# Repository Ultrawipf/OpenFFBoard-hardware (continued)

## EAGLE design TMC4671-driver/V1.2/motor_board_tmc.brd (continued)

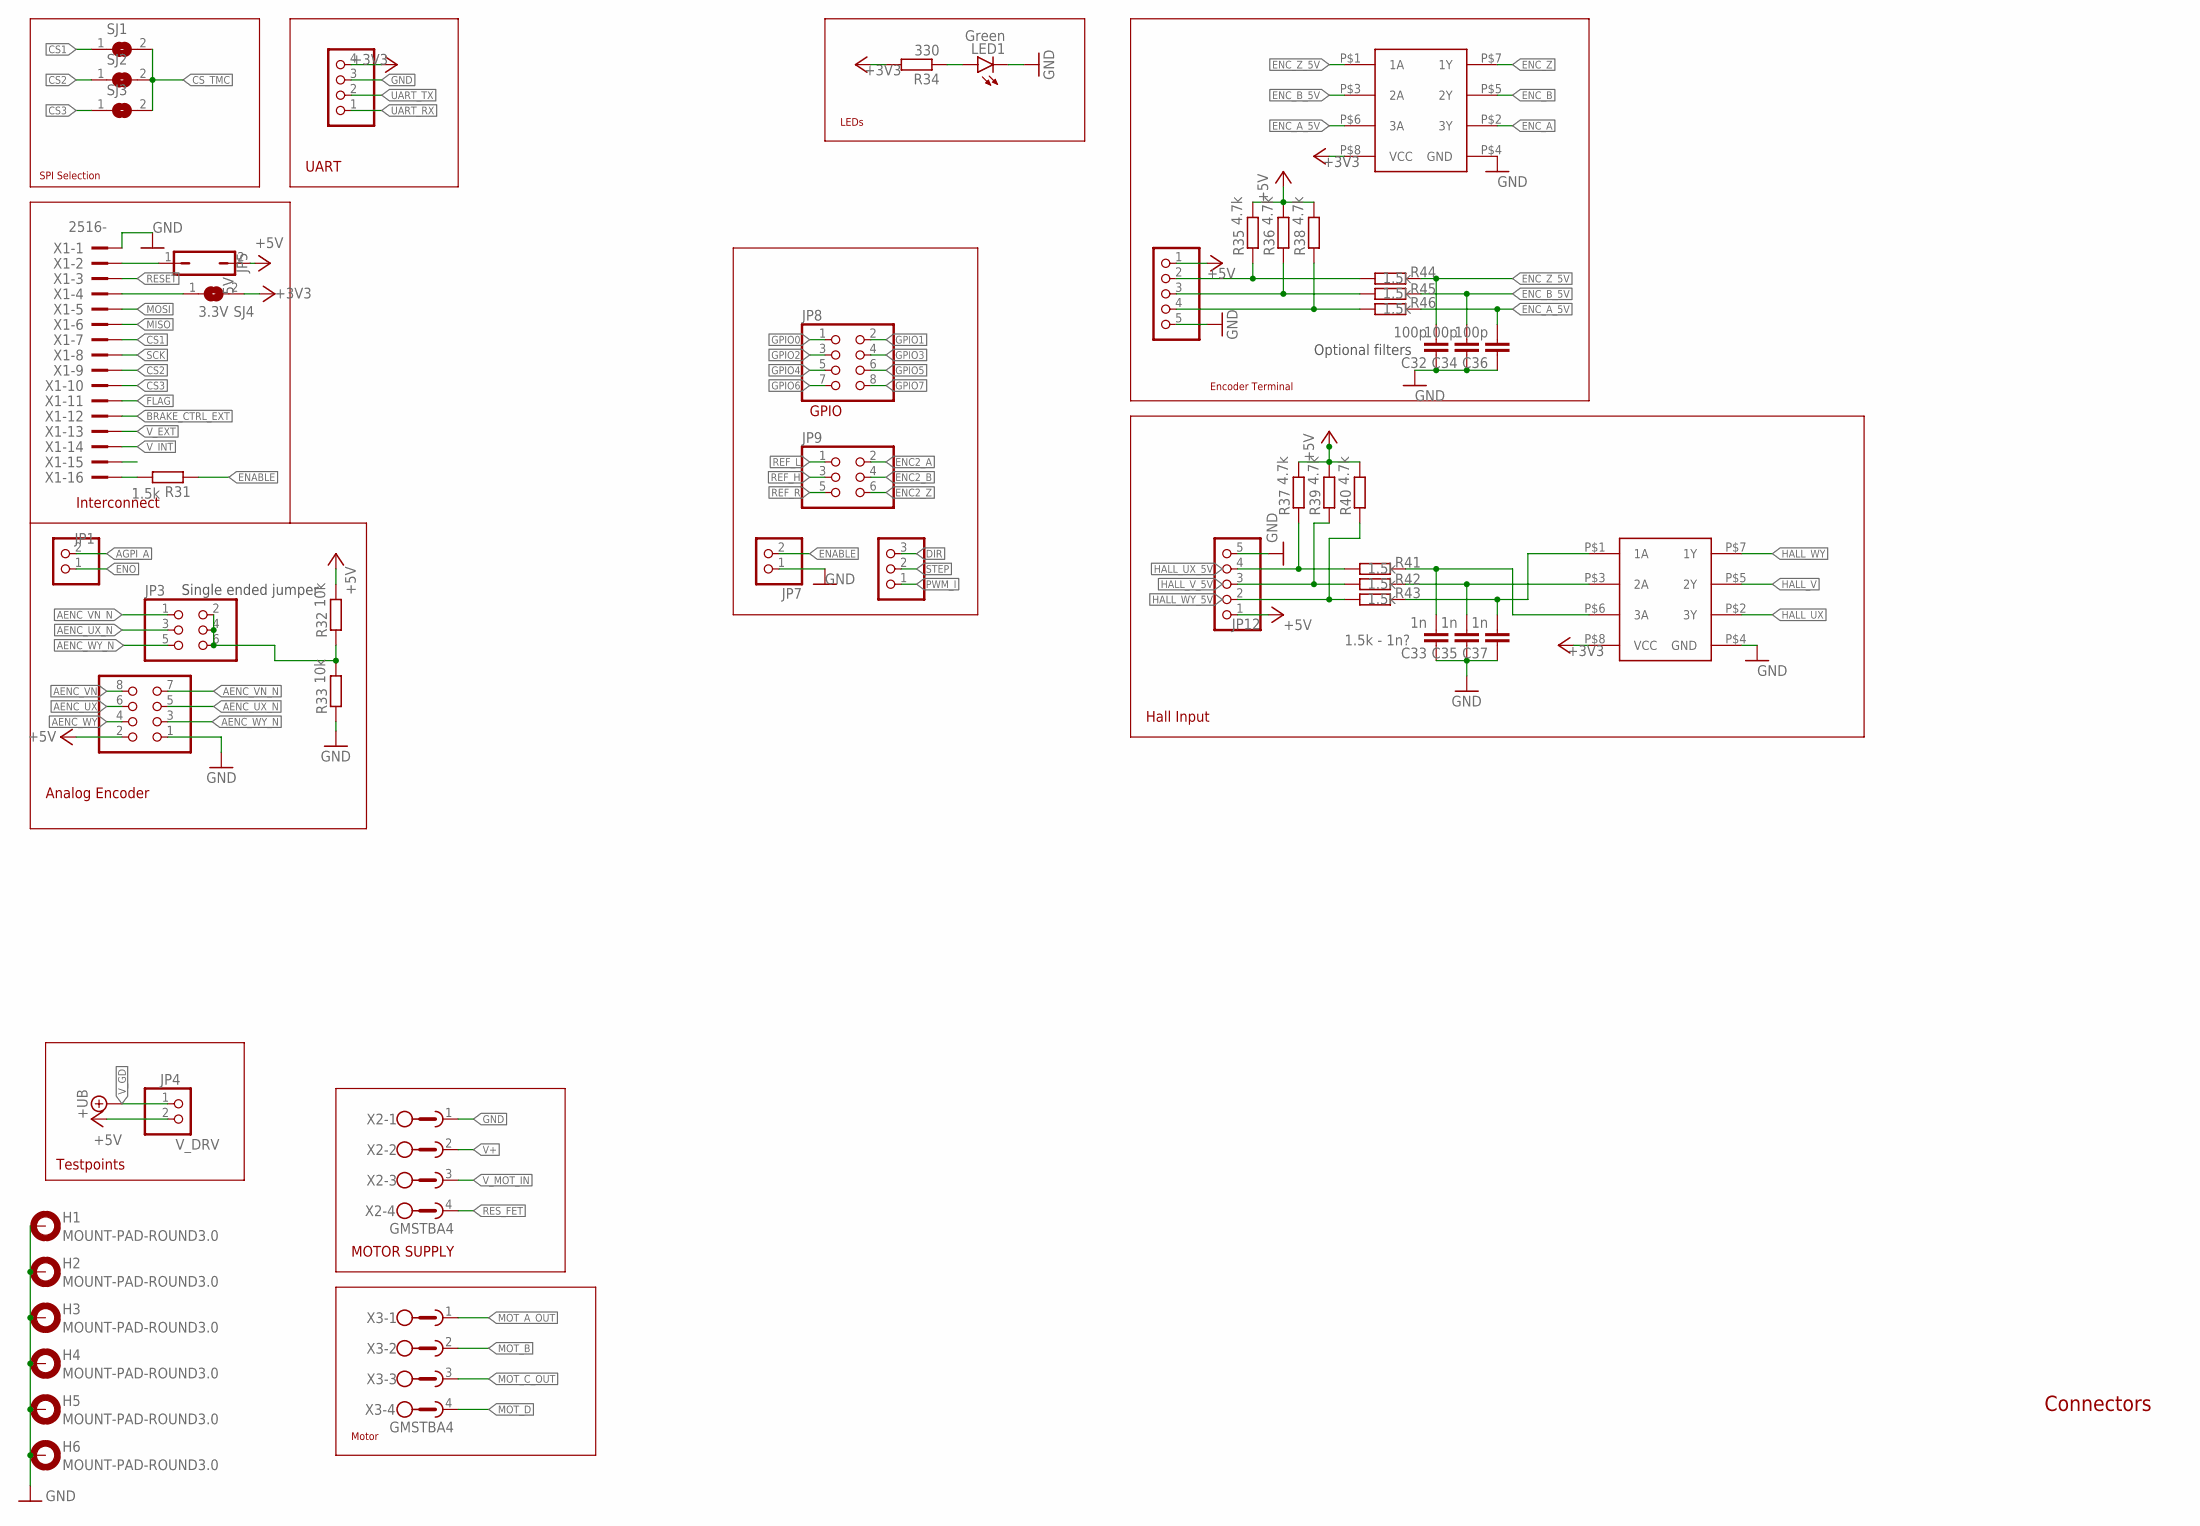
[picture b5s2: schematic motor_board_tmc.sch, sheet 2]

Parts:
C32, C34, C36: 100p; C0603
C33, C35, C37: 1n; C0603
H1, H2, H3, H4, H5, H6: MOUNT-PAD-ROUND3.0; 3,0-PAD
JP1, JP7: PINHD-1X2; 1X02
JP2, JP8: PINHD-2X4; 2X04
JP3, JP9: PINHD-2X3; 2X03
JP4: V_DRV; 1X02
JP5: 5V; JP1
JP6: PINHD-1X4; 1X04
JP10: PINHD-1X3; 1X03
JP11, JP12: PINHD-1X5; 1X05
LED1: Green; SML0805
R31, R41, R42, R43, R44, R45, R46: 1.5k; R0603
R32, R33: 10k; R0603
R34: 330; R0603
R35, R36, R37, R38, R39, R40: 4.7k; R0603
SJ1, SJ2, SJ3: SJ
SJ4: 3.3V; SJ
U18, U19: NC7NZ17K8X-3-BUFFER; VFSOP-8
X1: 2516-; PAK100/2500-16
X2, X3: GMSTBA4

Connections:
+3V3: JP6.4, R34.2, SJ4.2, U18.P$8 (VCC), U19.P$8 (VCC); also elsewhere on the board
+5V: JP2.2, JP4.2, JP5.2, JP11.1, JP12.1, R32.2, R35.2, R36.2, R37.2, R38.2, R39.2, R40.2; also elsewhere on the board
AENC_UX: JP2.6; also elsewhere on the board
AENC_UX_N: JP2.5, JP3.3; also elsewhere on the board
AENC_VN: JP2.8; also elsewhere on the board
AENC_VN_N: JP2.7, JP3.1; also elsewhere on the board
AENC_WY: JP2.4; also elsewhere on the board
AENC_WY_N: JP2.3, JP3.5; also elsewhere on the board
AGPI_A: JP1.2; also elsewhere on the board
BRAKE_CTRL_EXT: X1.12; also elsewhere on the board
CS1: SJ1.1, X1.7
CS2: SJ2.1, X1.9
CS3: SJ3.1, X1.10
CS_TMC: SJ1.2, SJ2.2, SJ3.2; also elsewhere on the board
DIR: JP10.3; also elsewhere on the board
ENABLE: JP7.2, R31.1; also elsewhere on the board
ENC2_A: JP9.2; also elsewhere on the board
ENC2_B: JP9.4; also elsewhere on the board
ENC2_Z: JP9.6; also elsewhere on the board
ENC_A: U18.P$2 (3Y); also elsewhere on the board
ENC_A_5V: C36.2, R46.1, U18.P$6 (3A)
ENC_B: U18.P$5 (2Y); also elsewhere on the board
ENC_B_5V: C34.2, R45.1, U18.P$3 (2A)
ENC_Z: U18.P$7 (1Y); also elsewhere on the board
ENC_Z_5V: C32.2, R44.1, U18.P$1 (1A)
ENO: JP1.1; also elsewhere on the board
FLAG: X1.11; also elsewhere on the board
GND: C32.1, C33.1, C34.1, C35.1, C36.1, C37.1, H1.B3,0, H2.B3,0, H3.B3,0, H4.B3,0, H5.B3,0, H6.B3,0, JP2.1, JP6.3, JP7.1, JP11.5, JP12.5, LED1.C, R33.1, U18.P$4 (GND), U19.P$4 (GND), X1.1, X2.1; also elsewhere on the board
GPIO0: JP8.1; also elsewhere on the board
GPIO1: JP8.2; also elsewhere on the board
GPIO2: JP8.3; also elsewhere on the board
GPIO3: JP8.4; also elsewhere on the board
GPIO4: JP8.5; also elsewhere on the board
GPIO5: JP8.6; also elsewhere on the board
GPIO6: JP8.7; also elsewhere on the board
GPIO7: JP8.8; also elsewhere on the board
HALL_UX: U19.P$2 (3Y); also elsewhere on the board
HALL_UX_5V: C33.2, R41.1, U19.P$6 (3A)
HALL_V: U19.P$5 (2Y); also elsewhere on the board
HALL_V_5V: C35.2, R42.1, U19.P$3 (2A)
HALL_WY: U19.P$7 (1Y); also elsewhere on the board
HALL_WY_5V: C37.2, R43.1, U19.P$1 (1A)
MISO: X1.6; also elsewhere on the board
MOSI: X1.5; also elsewhere on the board
MOT_A_OUT: X3.1; also elsewhere on the board
MOT_B: X3.2; also elsewhere on the board
MOT_C_OUT: X3.3; also elsewhere on the board
MOT_D: X3.4; also elsewhere on the board
unnamed: JP12.4, R37.1, R41.2
unnamed: JP12.3, R39.1, R42.2
unnamed: JP11.4, R38.1, R46.2
unnamed: LED1.A, R34.1
unnamed: JP11.3, R36.1, R45.2
unnamed: JP11.2, R35.1, R44.2
unnamed: JP12.2, R40.1, R43.2
unnamed: R31.2, X1.16
unnamed: SJ4.1, X1.4
unnamed: JP3.2, JP3.4, JP3.6, R32.1, R33.2
unnamed: JP5.1, X1.2
PWM_I: JP10.1; also elsewhere on the board
REF_H: JP9.3; also elsewhere on the board
REF_L: JP9.1; also elsewhere on the board
REF_R: JP9.5; also elsewhere on the board
RESET: X1.3; also elsewhere on the board
RES_FET: X2.4; also elsewhere on the board
SCK: X1.8; also elsewhere on the board
STEP: JP10.2; also elsewhere on the board
UART_RX: JP6.1; also elsewhere on the board
UART_TX: JP6.2; also elsewhere on the board
V+: X2.2; also elsewhere on the board
V_EXT: X1.13; also elsewhere on the board
V_GD: JP4.1; also elsewhere on the board
V_INT: X1.14; also elsewhere on the board
V_MOT_IN: X2.3; also elsewhere on the board

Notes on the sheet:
Motor
Encoder Terminal
Hall Input
GPIO
MOTOR SUPPLY
Interconnect
UART
SPI Selection
LEDs
Connectors
Testpoints
Analog Encoder
Single ended jumper
1.5k - 1n?
Optional filters

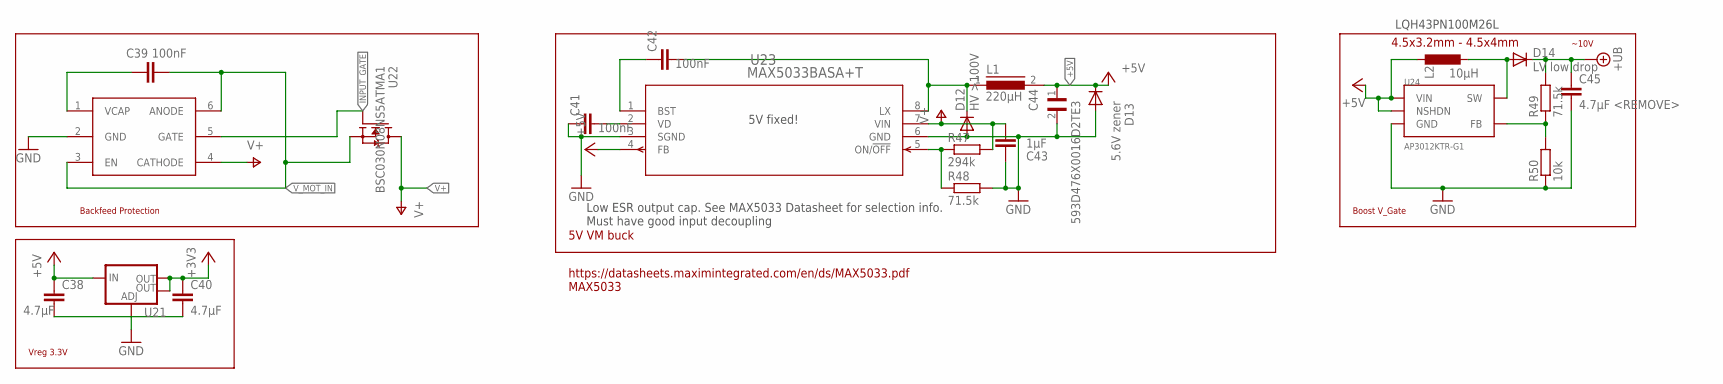
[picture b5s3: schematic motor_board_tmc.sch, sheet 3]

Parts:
C38, C40: 4.7µF; C0805
C39: 100nF; C0805
C41, C42: 100nF; C0603
C43: 1µF; C1206
C44: 593D476X0016D2TE3; CAPPM7343X310N
C45: 4.7µF <REMOVE>; C0805
D12: HV >100V; SOD-123FL
D13: 5.6V zener; SOD-123FL
D14: LV low drop; SOD-123FL
L1: 220µH; 8MMINDUCTOR
L2: 10µH; L4532P
R47: 294k; R0805
R48, R49: 71.5k; R0805
R50: 10k; R0603
U20: LM74700-Q1; SOT23-6
U21: V_REG_LM1117SOT223; SOT223
U22: BSC030N08NS5ATMA1; MOSFET_BSC093N04LSGATMA1
U23: MAX5033BASA+T; 21-0041B_8_MXM
U24: AP3012KTR-G1; SOT23-5L

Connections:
+3V3: C40.1, U21.2 (OUT), U21.4 (OUT); also elsewhere on the board
+5V: C38.1, C44.1, D13.C, L1.2, L2.1, U21.3 (IN), U23.4 (FB), U24.4 (NSHDN), U24.5 (VIN); also elsewhere on the board
GND: C38.2, C40.2, C41.1, C43.1, C44.2, C45.2, D12.A, D13.A, R48.2, R50.1, U20.2 (GND), U21.1 (ADJ), U23.3 (SGND), U23.6 (GND), U24.2 (GND); also elsewhere on the board
INPUT_GATE: U20.5 (GATE), U22.4 (G)
unnamed: R49.1, R50.2, U24.3 (FB)
unnamed: D14.A, L2.2, U24.1 (SW)
unnamed: C42.2, D12.C, L1.1, U23.8 (LX)
unnamed: C42.1, U23.1 (BST)
unnamed: R47.1, R48.1, U23.5 (ON/!OFF)
unnamed: C39.1, U20.1 (VCAP)
unnamed: C41.2, U23.2 (VD)
V+: C43.2, R47.2, U20.4 (CATHODE), U22.5 (D), U23.7 (VIN); also elsewhere on the board
V_GD: C45.1, D14.C, R49.2; also elsewhere on the board
V_MOT_IN: C39.2, U20.3 (EN), U20.6 (ANODE), U22.1 (S), U22.2 (S), U22.3 (S); also elsewhere on the board

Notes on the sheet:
Vreg 3.3V
Backfeed Protection
Boost V_Gate
~10V
4.5x3.2mm - 4.5x4mm
5V VM buck
https://datasheets.maximintegrated.com/en/ds/MAX5033.pdf MAX5033
5V fixed!
LQH43PN100M26L
Low ESR output cap. See MAX5033 Datasheet for selection info. Must have good input decoupling

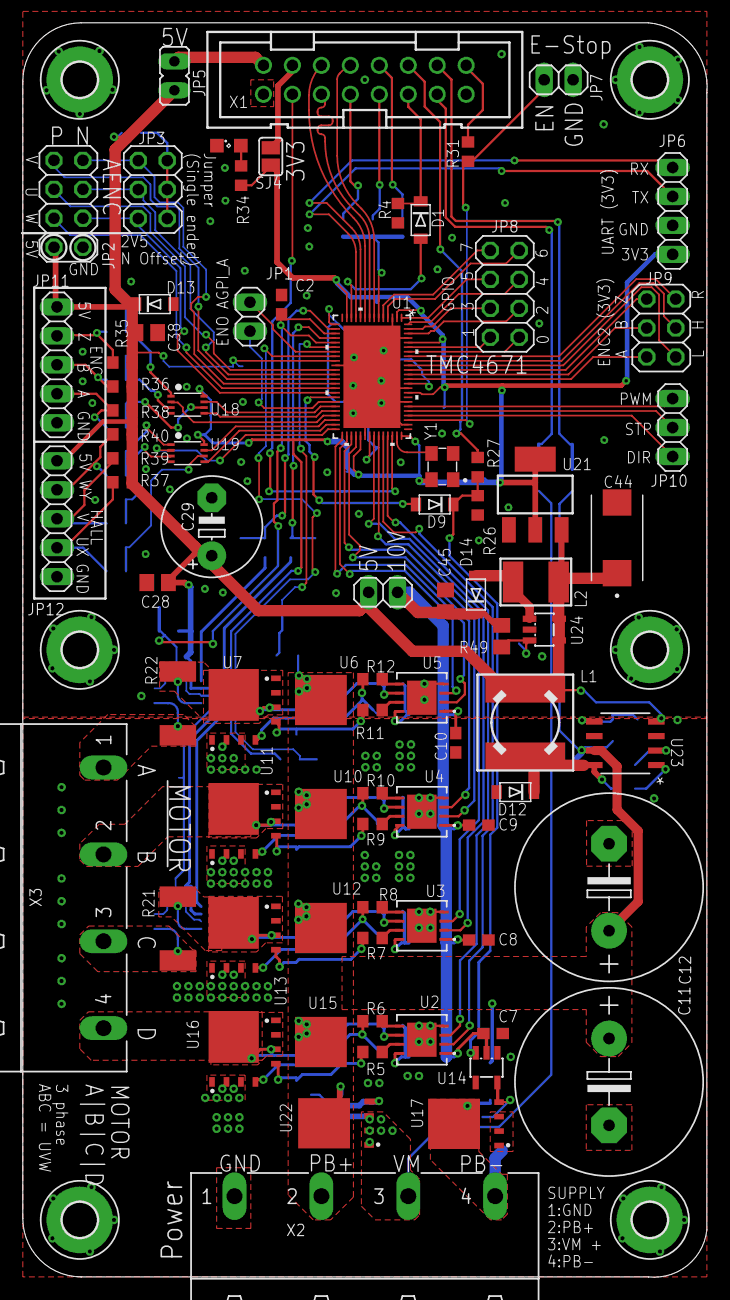
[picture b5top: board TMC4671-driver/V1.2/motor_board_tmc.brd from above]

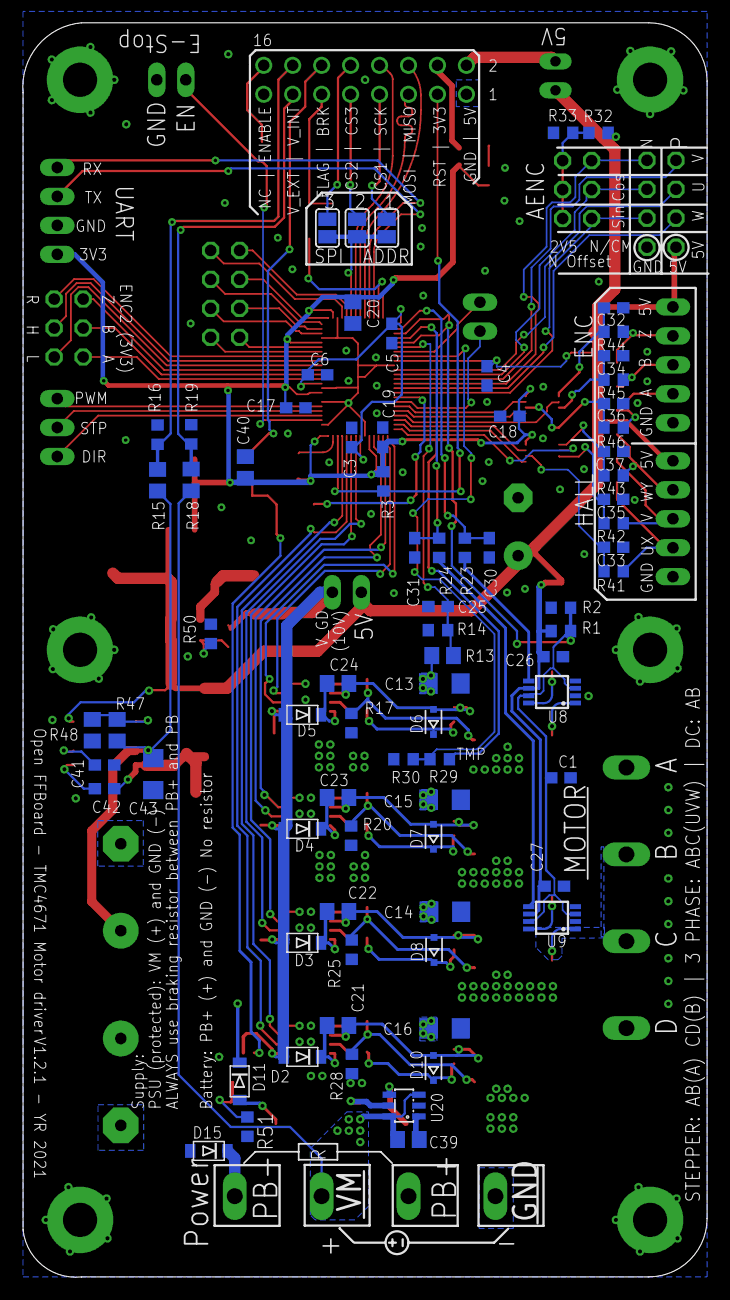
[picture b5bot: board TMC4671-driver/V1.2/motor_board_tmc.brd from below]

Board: 2 copper layers, 60.0 x 110.0 mm, 164 parts (78 on the bottom side), 125 nets.

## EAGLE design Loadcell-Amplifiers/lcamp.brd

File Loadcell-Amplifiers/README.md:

## INA333 3-wire Loadcell amplifier

Connections:
###
- Vin   :   3.3V/5V supply and load cell positive
- GND   :   GND and load cell negative
- IN    :   Load cell center/signal
- OUT   :   Amplified signal. Connect to ADC input

Gain setting: 10-1000, Clockwise rotation to increase
Offset: Clockwise to move the output up, ccw to move the output down to GND

Retune the offset when changing the gain and carefully check the output voltage to get the offset perfect.

The CPL and BOM files contain LCSC part numbers and be used on [JLCPCB](jlcpcb.com/).

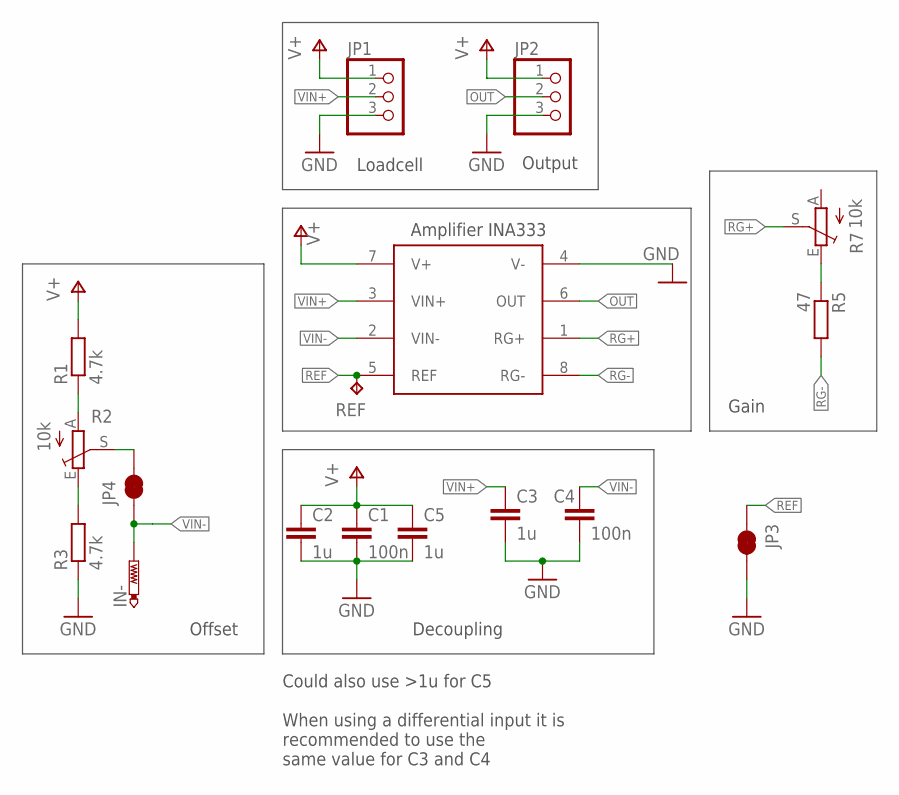
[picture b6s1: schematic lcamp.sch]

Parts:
C1, C4: 100n; C0603
C2, C3, C5: 1u; C0603
IN-: PTR1PAD1-13; P1-13
JP1, JP2: PINHD-1X3; 1X03
JP3, JP4: JUMPER-SMT_2_NC_TRACE_SILK; SMT-JUMPER_2_NC_TRACE_SILK
R1, R3: 4.7k; R0603
R2, R7: 10k; RJ9W
R5: 47; R0603
REF: TPB1,27; B1,27
U1: INA333MSOP8; MSOP8

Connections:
GND: C1.2, C2.2, C3.2, C4.2, C5.2, JP1.3, JP2.3, JP3.2, R3.1, U1.4 (V-)
unnamed: R5.1, R7.E
unnamed: R1.1, R2.A
unnamed: R2.E, R3.2
unnamed: JP4.2, R2.S
OUT: JP2.2, U1.6 (OUT)
REF: JP3.1, REF.TP, U1.5 (REF)
RG+: R7.S, U1.1 (RG+)
RG-: R5.2, U1.8 (RG-)
V+: C1.1, C2.1, C5.1, JP1.1, JP2.1, R1.2, U1.7 (V+)
VIN+: C3.1, JP1.2, U1.3 (VIN+)
VIN-: C4.1, IN-.TP, JP4.1, U1.2 (VIN-)

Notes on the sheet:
Offset
Gain
Loadcell
Output
Amplifier INA333
Decoupling
Could also use >1u for C5 When using a differential input it is recommended to use the same value for C3 and C4

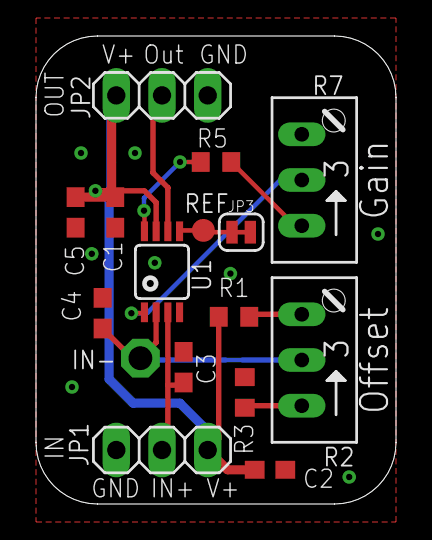
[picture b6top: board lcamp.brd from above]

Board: 2 copper layers, 20.0 x 26.0 mm, 17 parts (1 on the bottom side), 12 nets.

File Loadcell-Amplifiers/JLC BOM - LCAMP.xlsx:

Comment | Designator | Footprint | LCSC Part #
INA333 | U1 | MSOP-8 | C19450
10k pot | R2,R7 | THT | C118954
1µ Capacitor | C2,C3,C5 | C0603 | C15849
4.7k Resistor | R1, R3 | R0603 | C23162
47 Ohm Resistor | R5 | R0603 | C23182
100n Capacitor | C4, C1 | C0603 | C14663

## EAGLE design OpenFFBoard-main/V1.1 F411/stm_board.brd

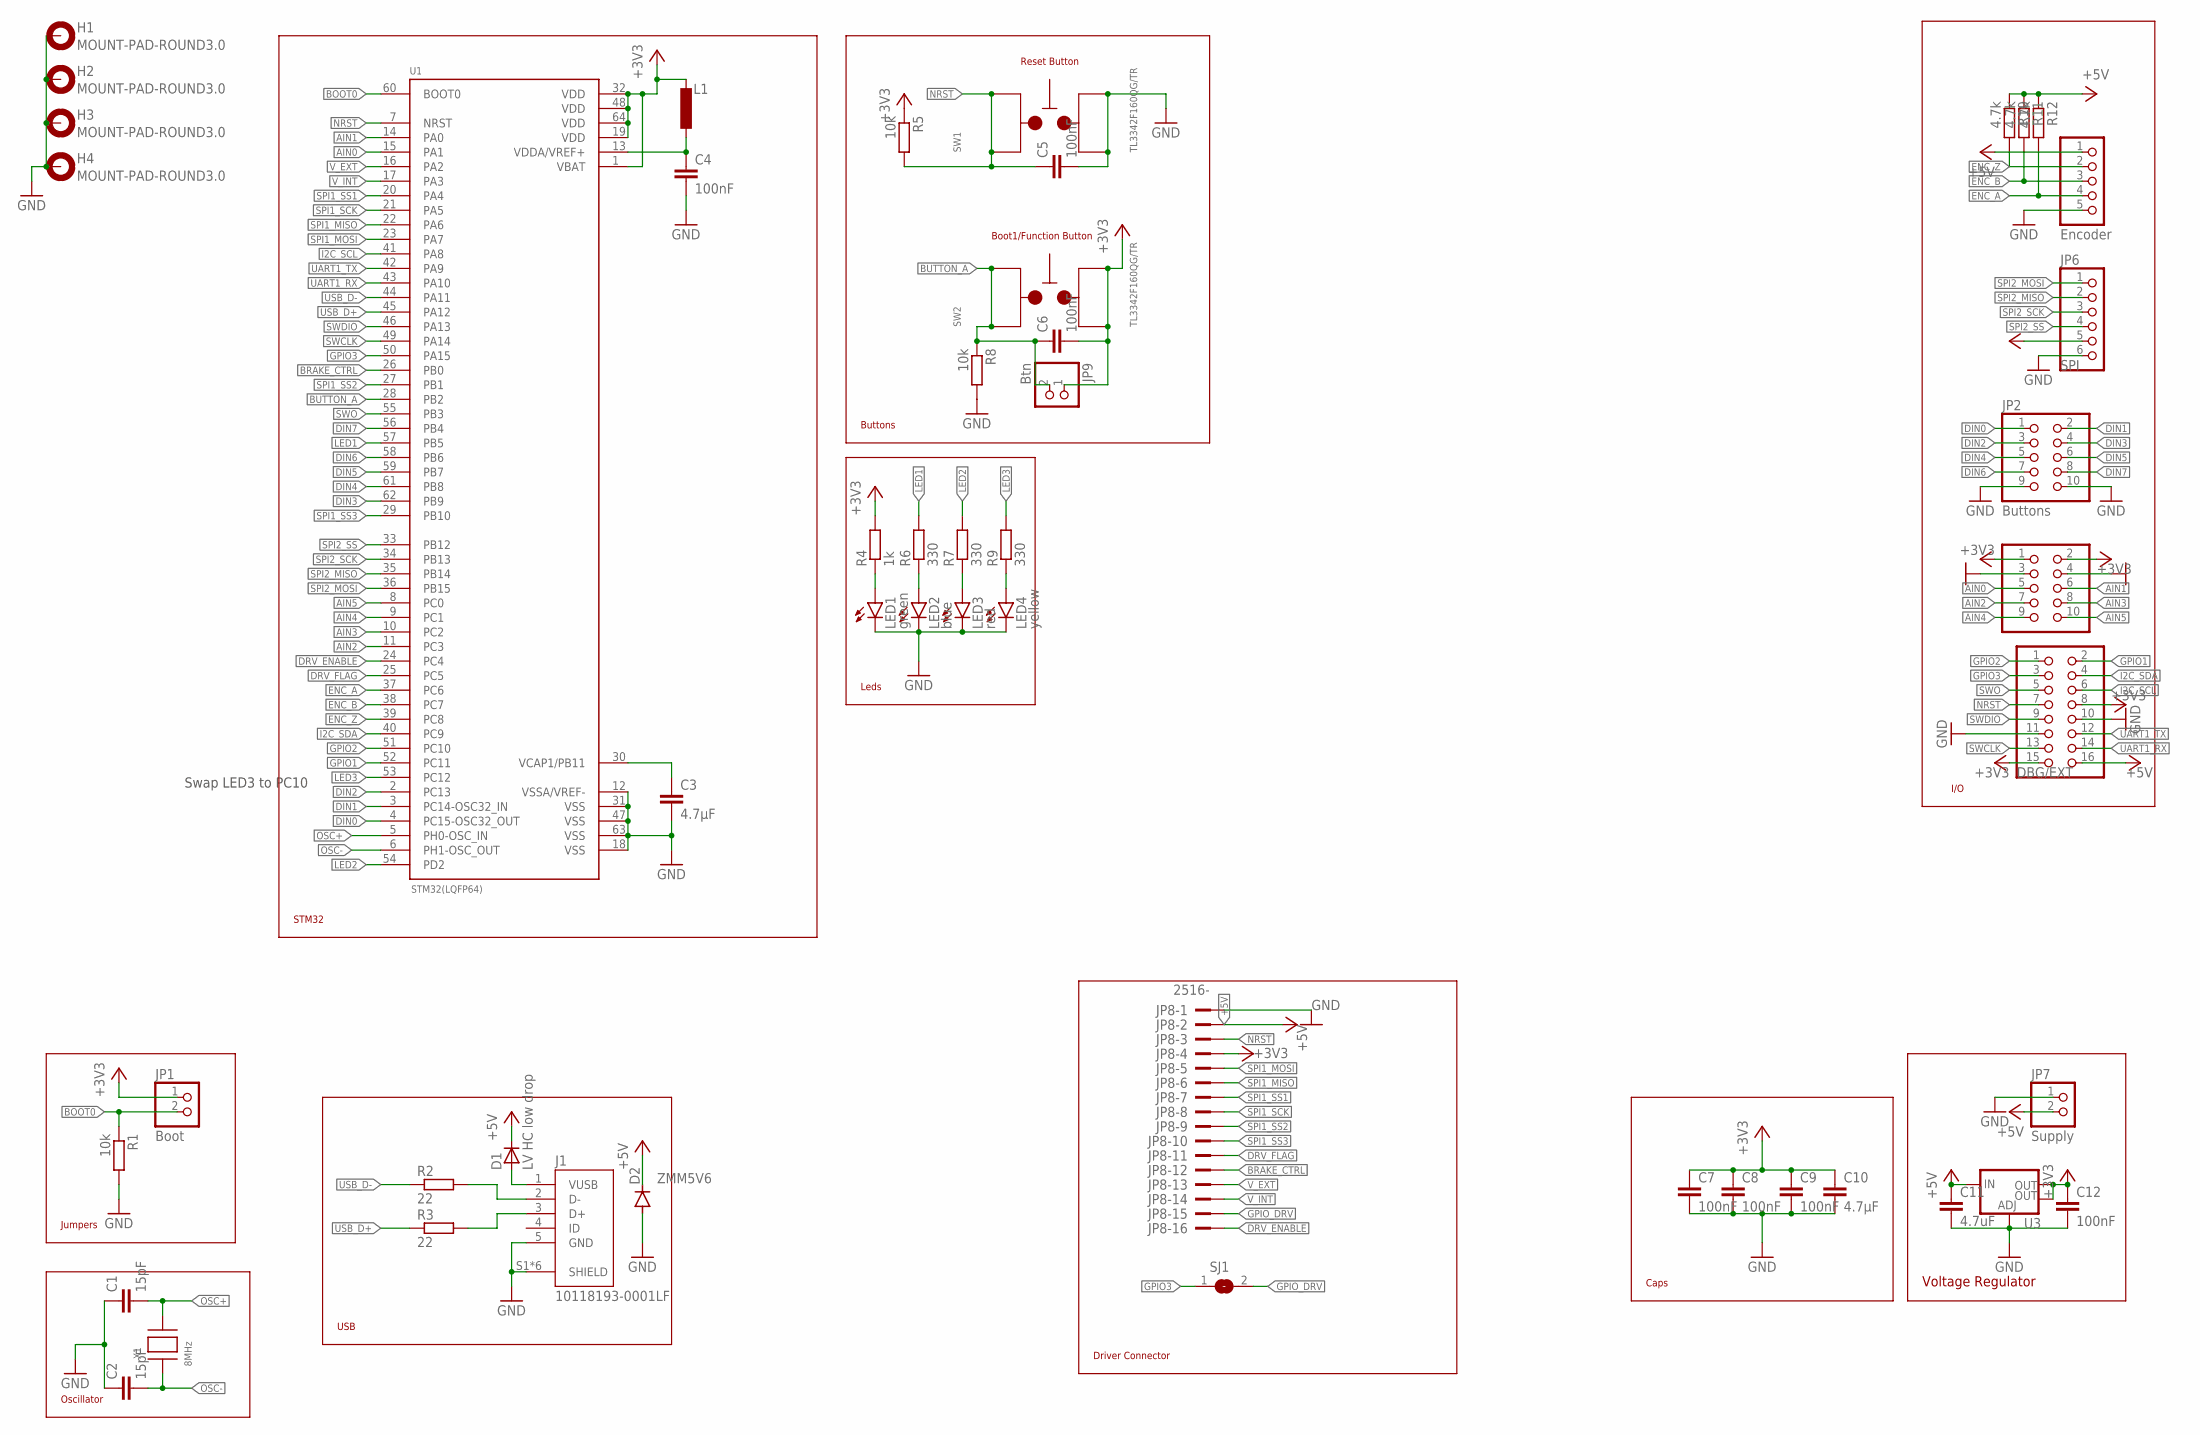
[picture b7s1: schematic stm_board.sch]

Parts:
C1, C2: 15pF; C0603
C3, C10: 4.7µF; C0805
C4, C5, C6, C7, C8, C9, C12: 100nF; C0603
C11: 4.7uF; C0805
D1: LV HC low drop; SMADIODE
D2: ZMM5V6; MINIMELF
H1, H2, H3, H4: MOUNT-PAD-ROUND3.0; 3,0-PAD
J1: 10118193-0001LF; FCI_10118193-0001LF
JP1: Boot; 1X02
JP2: Buttons; 2X05
JP3: Analog; 2X05
JP4: DBG/EXT; 2X08
JP5: Encoder; 1X05
JP6: SPI; 1X06
JP7: Supply; 1X02
JP8: 2516-; PAK100/2500-16
JP9: Btn; 1X02
L1: 2.2µH; L2012C
LED1: green; CHIPLED_0805
LED2: blue; CHIPLED_0805
LED3: red; CHIPLED_0805
LED4: yellow; CHIPLED_0805
R1, R5, R8: 10k; R0603
R2, R3: 22; R0603
R4: 1k; R0603
R6, R7, R9: 330; R0603
R10, R11, R12: 4.7k; R0603
SJ1: SJ
SW1, SW2: TL3342F160QG/TR
U1: STM32(LQFP64); QFP50P1200X1200X160-64N
U3: V_REG_LM1117SOT223; SOT223
X1: 8MHz; NX5032

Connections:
+3V3: C6.2, C7.1, C8.1, C9.1, C10.1, C12.1, JP1.1, JP3.1, JP3.2, JP4.8, JP4.15, JP6.5, JP8.4, JP9.1, L1.1, R4.2, R5.1, SW2.1, SW2.2, U1.1 (VBAT), U1.19 (VDD), U1.32 (VDD), U1.48 (VDD), U1.64 (VDD), U3.2 (OUT), U3.4 (OUT)
+5V: C11.1, D1.C, D2.C, JP4.16, JP5.1, JP7.2, JP8.2, R10.1, R11.1, R12.1, U3.3 (IN)
AIN0: JP3.5, U1.15 (PA1)
AIN1: JP3.6, U1.14 (PA0)
AIN2: JP3.7, U1.11 (PC3)
AIN3: JP3.8, U1.10 (PC2)
AIN4: JP3.9, U1.9 (PC1)
AIN5: JP3.10, U1.8 (PC0)
BOOT0: JP1.2, R1.1, U1.60 (BOOT0)
BRAKE_CTRL: JP8.12, U1.26 (PB0)
BUTTON_A: C6.1, JP9.2, R8.1, SW2.3, SW2.4, U1.28 (PB2)
DIN0: JP2.1, U1.4 (PC15-OSC32_OUT)
DIN1: JP2.2, U1.3 (PC14-OSC32_IN)
DIN2: JP2.3, U1.2 (PC13)
DIN3: JP2.4, U1.62 (PB9)
DIN4: JP2.5, U1.61 (PB8)
DIN5: JP2.6, U1.59 (PB7)
DIN6: JP2.7, U1.58 (PB6)
DIN7: JP2.8, U1.56 (PB4)
DRV_ENABLE: JP8.16, U1.24 (PC4)
DRV_FLAG: JP8.11, U1.25 (PC5)
ENC_A: JP5.4, R12.2, U1.37 (PC6)
ENC_B: JP5.3, R11.2, U1.38 (PC7)
ENC_Z: JP5.2, R10.2, U1.39 (PC8)
GND: C1.1, C2.1, C3.2, C4.2, C5.2, C7.2, C8.2, C9.2, C10.2, C11.2, C12.2, D2.A, H1.B3,0, H2.B3,0, H3.B3,0, H4.B3,0, J1.5 (GND), J1.S1 (SHIELD), J1.S2 (SHIELD), J1.S3 (SHIELD), J1.S4 (SHIELD), J1.S5 (SHIELD), J1.S6 (SHIELD), JP2.9, JP2.10, JP3.3, JP3.4, JP4.10, JP4.11, JP5.5, JP6.6, JP7.1, JP8.1, LED1.C, LED2.C, LED3.C, LED4.C, R1.2, R8.2, SW1.1, SW1.2, U1.12 (VSSA/VREF-), U1.18 (VSS), U1.31 (VSS), U1.47 (VSS), U1.63 (VSS), U3.1 (ADJ)
GPIO1: JP4.2, U1.52 (PC11)
GPIO2: JP4.1, U1.51 (PC10)
GPIO3: JP4.3, SJ1.1, U1.50 (PA15)
GPIO_DRV: JP8.15, SJ1.2
I2C_SCL: JP4.6, U1.41 (PA8)
I2C_SDA: JP4.4, U1.40 (PC9)
LED1: R6.2, U1.57 (PB5)
LED2: R7.2, U1.54 (PD2)
LED3: R9.2, U1.53 (PC12)
unnamed: D1.A, J1.1 (VUSB)
unnamed: LED4.A, R9.1
unnamed: C4.1, L1.2, U1.13 (VDDA/VREF+)
unnamed: C3.1, U1.30 (VCAP1/PB11)
unnamed: J1.2 (D-), R2.2
unnamed: J1.3 (D+), R3.2
unnamed: LED1.A, R4.1
unnamed: LED2.A, R6.1
unnamed: LED3.A, R7.1
NRST: C5.1, JP4.7, JP8.3, R5.2, SW1.3, SW1.4, U1.7 (NRST)
OSC+: C1.2, U1.5 (PH0-OSC_IN), X1.P$2
OSC-: C2.2, U1.6 (PH1-OSC_OUT), X1.P$1
SPI1_MISO: JP8.6, U1.22 (PA6)
SPI1_MOSI: JP8.5, U1.23 (PA7)
SPI1_SCK: JP8.8, U1.21 (PA5)
SPI1_SS1: JP8.7, U1.20 (PA4)
SPI1_SS2: JP8.9, U1.27 (PB1)
SPI1_SS3: JP8.10, U1.29 (PB10)
SPI2_MISO: JP6.2, U1.35 (PB14)
SPI2_MOSI: JP6.1, U1.36 (PB15)
SPI2_SCK: JP6.3, U1.34 (PB13)
SPI2_SS: JP6.4, U1.33 (PB12)
SWCLK: JP4.13, U1.49 (PA14)
SWDIO: JP4.9, U1.46 (PA13)
SWO: JP4.5, U1.55 (PB3)
UART1_RX: JP4.14, U1.43 (PA10)
UART1_TX: JP4.12, U1.42 (PA9)
USB_D+: R3.1, U1.45 (PA12)
USB_D-: R2.1, U1.44 (PA11)
V_EXT: JP8.13, U1.16 (PA2)
V_INT: JP8.14, U1.17 (PA3)

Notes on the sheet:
Oscillator
USB
Boot1/Function Button
Reset Button
Buttons
Jumpers
Leds
Voltage Regulator
I/O
Driver Connector
Caps
STM32
Swap LED3 to PC10

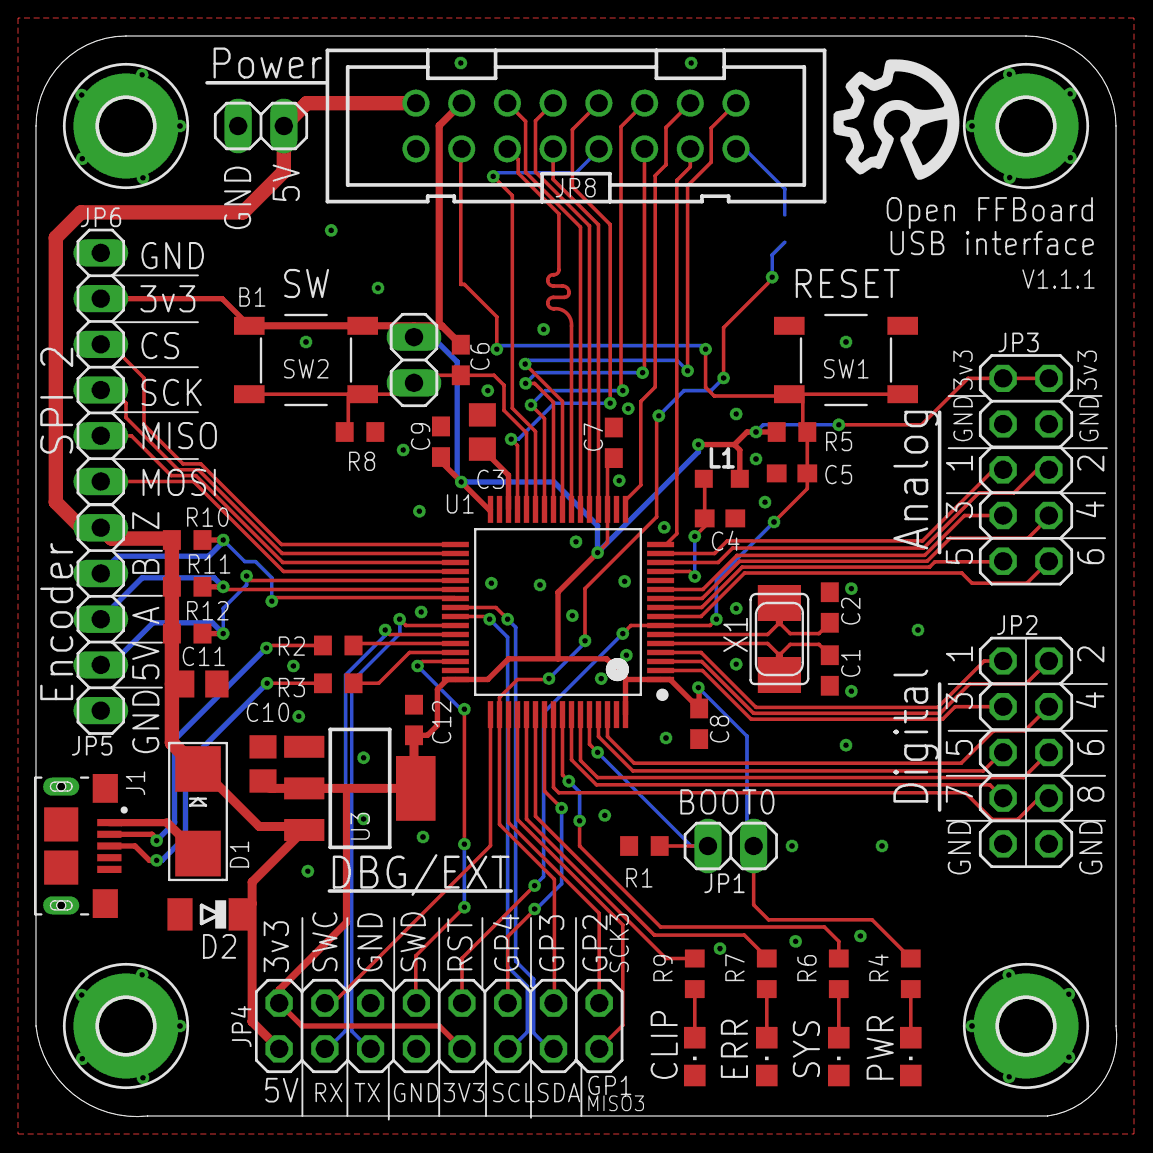
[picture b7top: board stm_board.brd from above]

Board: 2 copper layers, 60.0 x 60.0 mm, 51 parts (1 on the bottom side), 65 nets.

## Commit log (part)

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2020-03-21 Added TMC driver
2020-04-16 Changing clearances to 8 mil and renamed shunt amps
2020-08-17 Updated TMC4671 board to redesigned 1.2 version.
2020-09-19 Added 1.1.1 stm board
2020-10-19 Edited readme formatting
2020-10-19 Improved readme formatting
2020-10-19 Improved readme formatting (#1)
    Improved readme formatting
2020-10-22 Updated TMC Board. Fixed D12 value
2020-11-13 Updated STM Board to v1.2
2020-11-14 Fixed swapped PWM channel labels
2020-11-14 Added E-Stop cap
2020-12-06 Updated crystal capacitor value
2021-01-08 Fixed swapped sense resistor labels in BOM for TMC
2021-01-09 Update README.md
    fixed links
2021-01-10 Fixed tmc silkscreen (Resistor names, labels)
2021-02-11 Added F407 board schematic pdf
2021-04-18 Swapped encoder Z pin on F407 board
2021-09-26 Schematic for f407 updated
2021-12-13 Added load cell amplifier files
2022-01-14 Added files for Hall sensor TMC
2022-06-02 Added USB-C V1.2.3 ffboard
2022-06-23 Fixed error in TMC V1.2 bom
2022-06-23 Added 32 button SPI input module design files
2022-06-23 Added SPI buttons readme
2022-08-14 Removed C27 and C28 from BOM
2022-08-14 Added F407 V1.2.4 files
2022-08-17 Added mention of max5033busa
2022-08-31 Readme update
2022-11-25 Updated BOM for TMC V1.2.2 hall and STM V1.2.4
2022-12-29 Ported project from EAGLE to KiCad
    Minimal port with only the necessary changes to pass ERC and DRC.
2022-12-29 Moved kicad port folder inside 1.2.4 folder
2022-12-31 Cosmetic changes on silkscreen. No more warnings
2022-12-31 Added missing logo
2022-12-31 Consistent naming convention and font size on schematic
2022-12-31 Updated design constraints
2023-01-02 Generated manufacturing files
2023-02-11 SPI button update
2023-02-11 Added BISS-C adapter
2023-02-13 License update to subfolder
2023-04-03 Made F407 pin1 marker more visible
2023-07-16 Renamed CLIP LED to FFB
2023-07-26 Updated links
2023-07-26 Replaces 2.2r with 22r in v1.2.2 tmc
2023-09-16 Added TMC 1.3.3 version
2025-03-03 Updated SPI buttons to v1.2
2025-03-03 Added lasercut case
2025-04-10 Added F407 1.2.4 3D models
